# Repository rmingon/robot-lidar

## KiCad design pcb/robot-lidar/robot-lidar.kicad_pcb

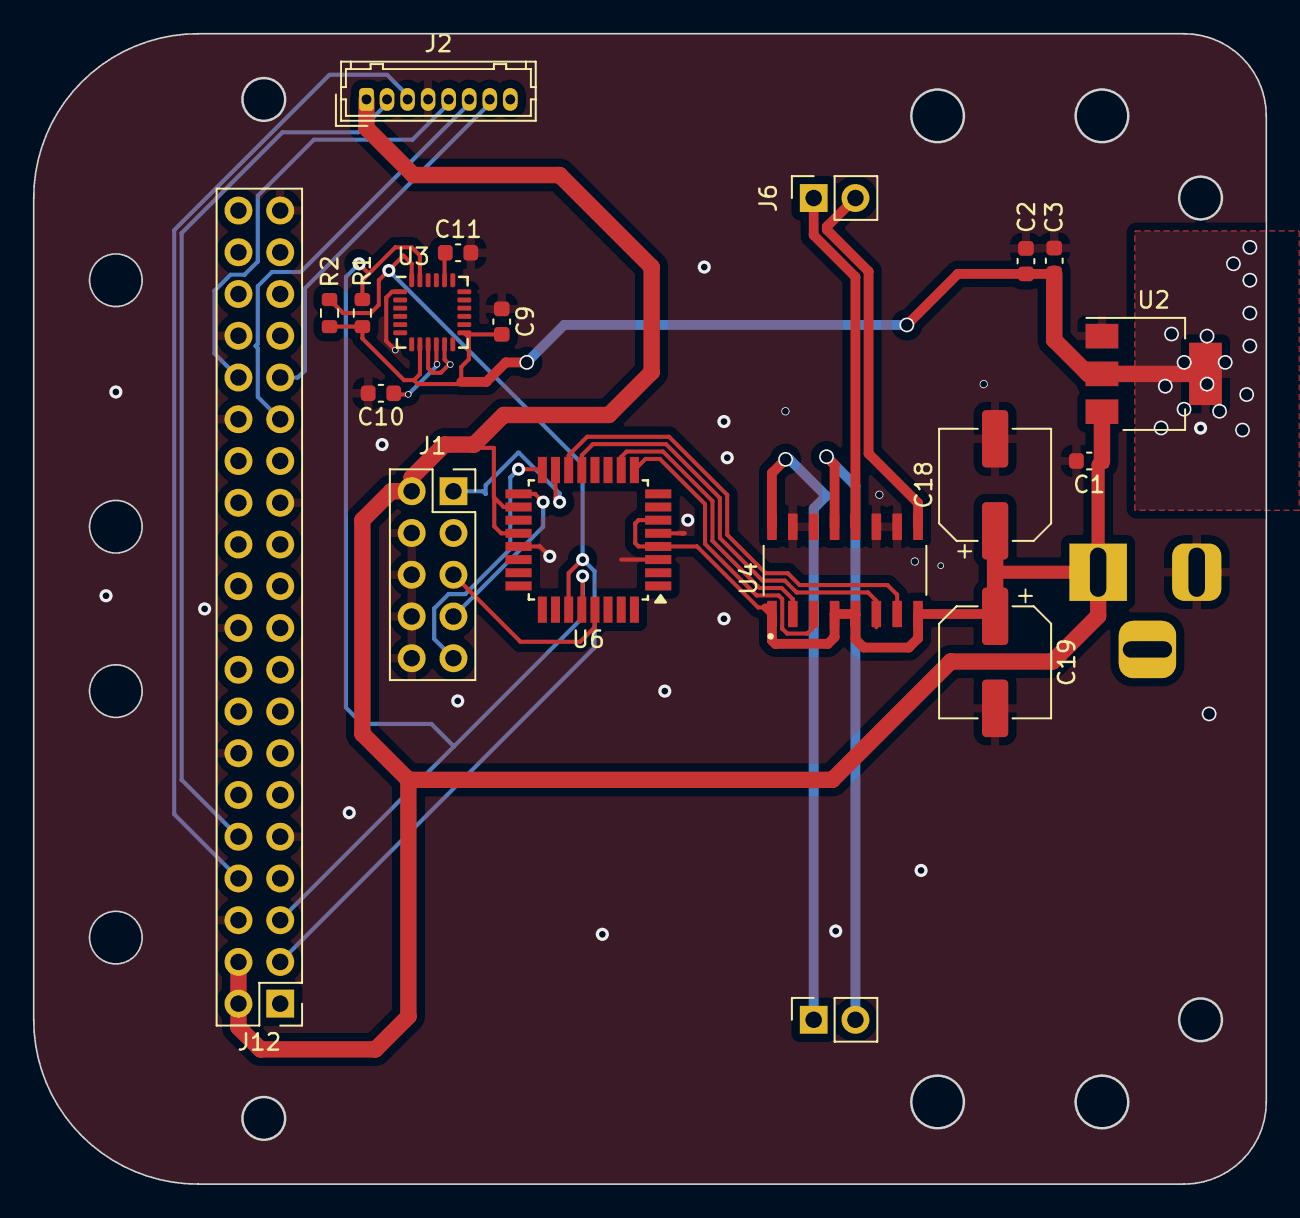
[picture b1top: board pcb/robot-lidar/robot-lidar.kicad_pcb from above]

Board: 2 copper layers, 75.0 x 70.0 mm, 20 parts (1 on the bottom side), 24 nets.

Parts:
C1: 1 uf; C_0603_1608Metric
C2: 1uf; C_0603_1608Metric
C3: 10 uf; C_0603_1608Metric
C9, C10, C11: C; C_0603_1608Metric
C18, C19: C_Polarized_Small; CP_Elec_6.3x4.9
J1: AVR-ISP-10; PinSocket_2x05_P2.54mm_Vertical
J2: YLIDAR X4; Hirose_DF13-08P-1.25DSA_1x08_P1.25mm_Vertical
J3: Jack-DC; BarrelJack_Horizontal
J5, J6: Conn_01x02; PinSocket_1x02_P2.54mm_Vertical
J12: Conn_02x20_Odd_Even; PinHeader_2x20_P2.54mm_Vertical
R1, R2: R_Small; R_0603_1608Metric
U2: LM317-3.3_SOT-223; SOT-223-3_TabPin2
U3: MPU-6050; InvenSense_QFN-24_4x4mm_P0.5mm
U4: MX1508; SOIC127P600X177-16N
U6: ATmega328P-A; TQFP-32_7x7mm_P0.8mm

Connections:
+3V3: C2.1, C3.1, C9.2, R1.1, R2.1, U2.2 (VO), U3.8 (VDDIO), U3.13 (VDD)
+5V: C1.1, C18.1, C19.1, J1.2 (VCC), J2.1, J3.1, J12.2, J12.4, U2.3 (VI), U4.1 (VCC1), U4.4 (VDD1), U4.5 (VCC2), U4.8 (VDD2), U6.4 (VCC), U6.6 (VCC), U6.18 (AVCC), U6.20 (AREF)
DEV_EN: J2.6, J12.29
GND: C1.2, C2.2, C3.2, C9.1, C10.2, C11.2, C18.2, C19.2, J1.4 (GND), J1.6 (GND), J1.8 (GND), J1.10 (GND), J2.4, J3.2, J12.6, J12.9, J12.14, J12.20, J12.25, J12.30, J12.34, J12.39, U2.1 (ADJ), U3.1 (CLKIN), U3.9 (AD0), U3.11 (FSYNC), U3.18 (GND), U4.10 (AGND2), U4.11 (PGND2), U4.14 (AGND1), U4.15 (PGND1), U6.3 (GND), U6.5 (GND), U6.21 (GND)
MISO: J1.9 (MISO), U6.16 (PB4)
MOSI: J1.1 (MOSI), U6.15 (PB3)
MOTOR_1_A: U4.2 (INA1), U6.10 (PD6)
MOTOR_1_B: U4.3 (INB1), U6.9 (PD5)
MOTOR_2_A: U4.6 (INA2), U6.13 (PB1)
MOTOR_2_B: U4.7 (INB2), U6.14 (PB2)
M_EN: J2.7, J12.31
M_SCTR: J2.5, J12.32
unnamed: J5.1, U4.16 (OUTA1)
unnamed: J5.2, U4.13 (OUTB1)
unnamed: J6.1, U4.12 (OUTA2)
unnamed: J6.2, U4.9 (OUTB2)
unnamed: C11.1, U3.20 (CPOUT)
unnamed: C10.1, U3.10 (REGOUT)
RST: J1.5 (~RST), U6.29 (~RESET/PC6)
SCK: J1.7 (SCK), U6.17 (PB5)
SCL: J12.5, R1.2, U3.23 (SCL), U6.28 (PC5)
SDA: J12.3, R2.2, U3.24 (SDA), U6.27 (PC4)
UART_RX: J2.2, J12.10
UART_TX: J2.3, J12.8

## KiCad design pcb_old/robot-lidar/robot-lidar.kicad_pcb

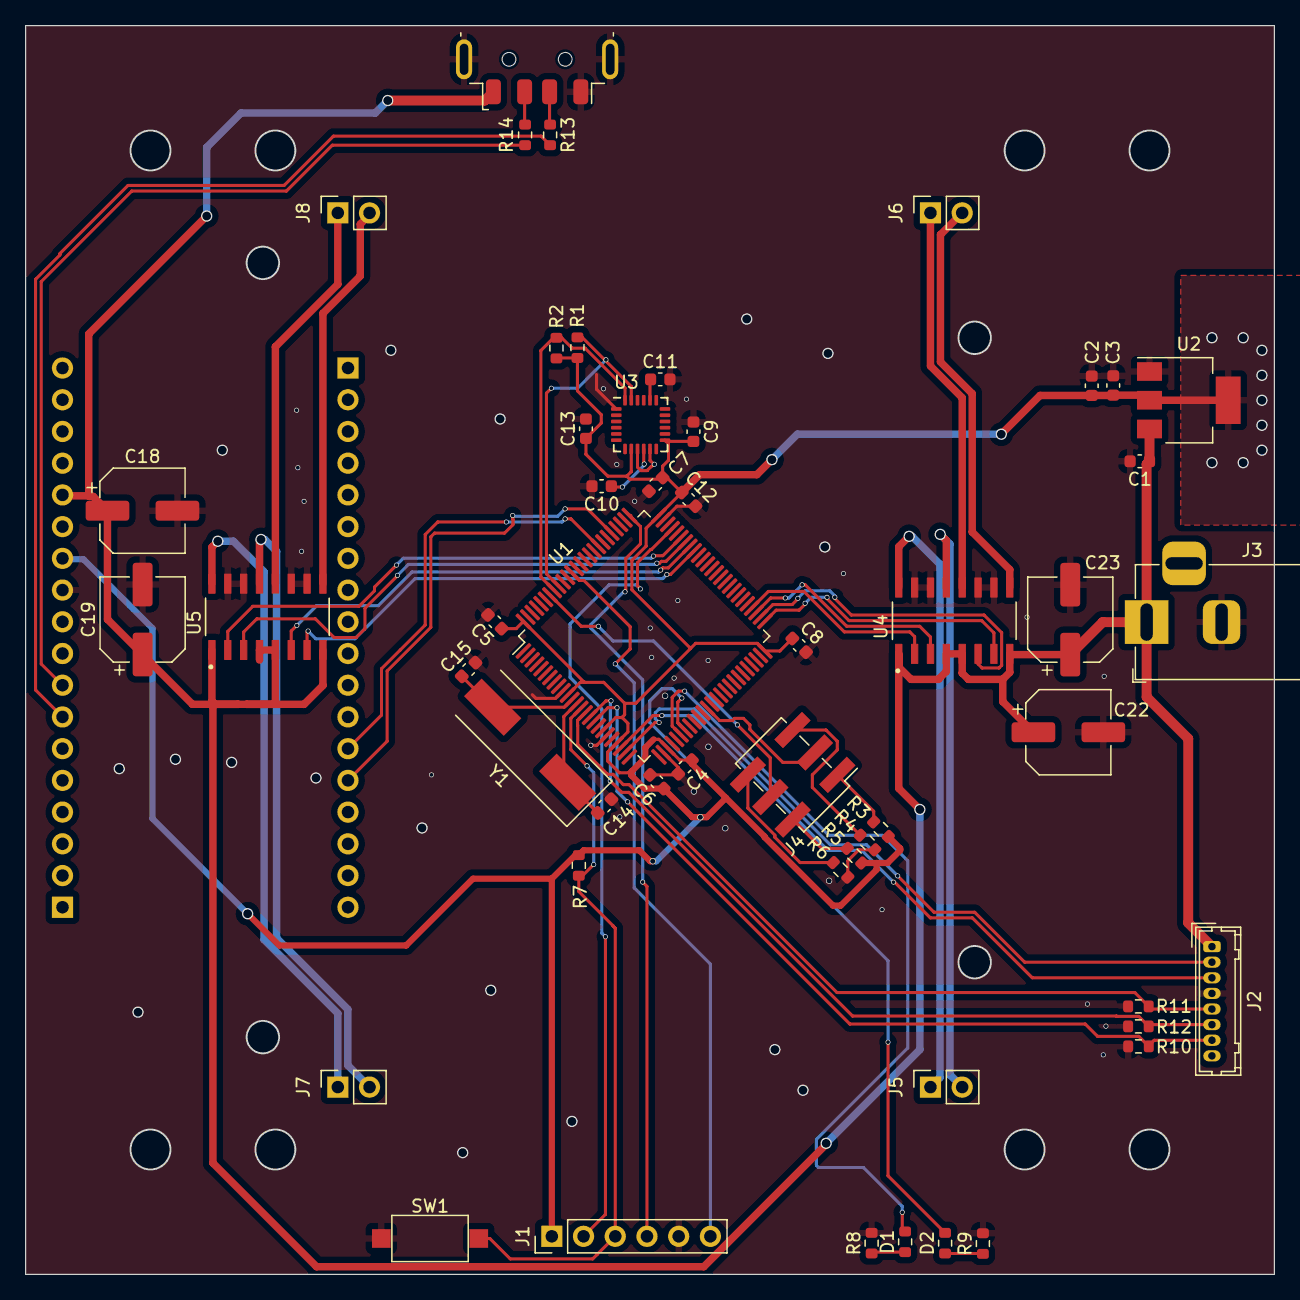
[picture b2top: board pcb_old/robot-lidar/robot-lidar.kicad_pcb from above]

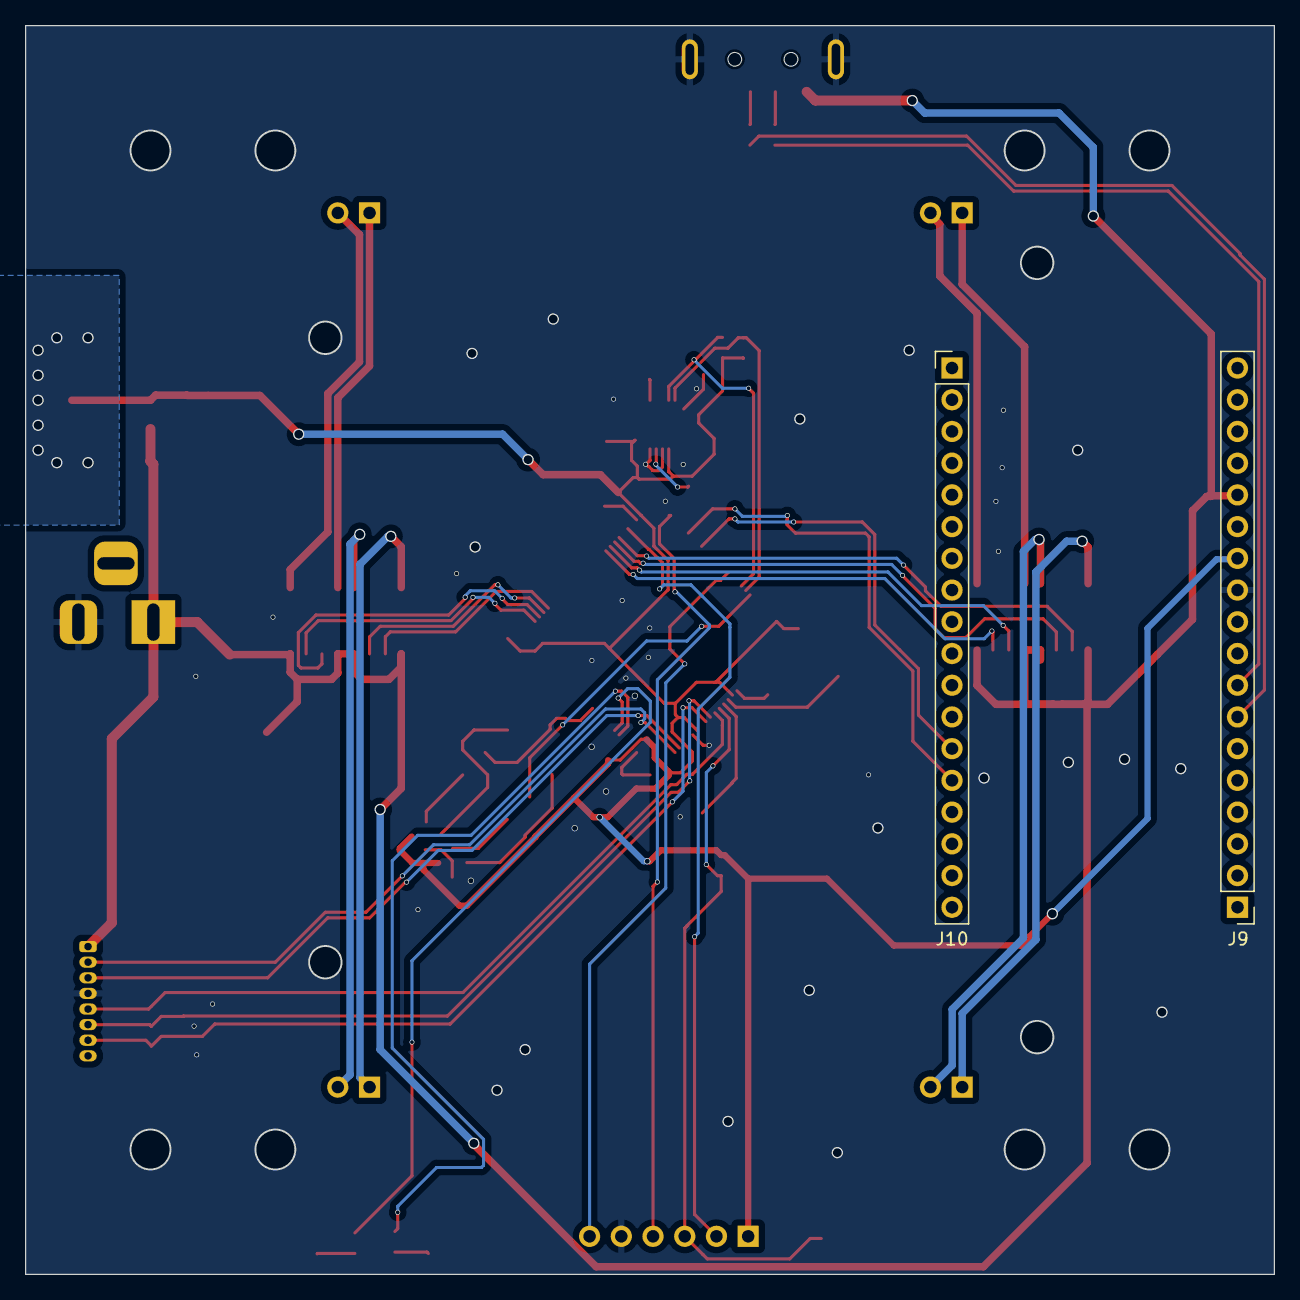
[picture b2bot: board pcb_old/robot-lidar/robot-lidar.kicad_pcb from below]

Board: 2 copper layers, 100.0 x 100.0 mm, 53 parts (2 on the bottom side), 50 nets.

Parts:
C1, C4, C5, C6, C7, C8, C12, C13: 1 uf; C_0603_1608Metric
C2: 1uf; C_0603_1608Metric
C3: 10 uf; C_0603_1608Metric
C9, C10, C11: C; C_0603_1608Metric
C14, C15: 0.1uF; C_0603_1608Metric
C18, C19, C22, C23: C_Polarized_Small; CP_Elec_6.3x4.9
D1, D2: LED_Small; R_0603_1608Metric
J1: Conn_ARM_SWD_TagConnect_TC2030; PinHeader_1x06_P2.54mm_Vertical
J2: YLIDAR X4; Hirose_DF13-08P-1.25DSA_1x08_P1.25mm_Vertical
J3: Jack-DC; BarrelJack_Horizontal
J4: Conn_02x03_Odd_Even; PinHeader_2x03_P2.54mm_Vertical_SMD
J5, J6, J7, J8: Conn_01x02; PinSocket_1x02_P2.54mm_Vertical
J9, J10: Conn_01x18; PinHeader_1x18_P2.54mm_Vertical
J11: USB_A; USB_A_Molex_48037-2200_Horizontal
R1, R2: R_Small; R_0603_1608Metric
R3, R4, R5, R6, R7: 10k; R_0603_1608Metric
R8, R9: 2k; R_0603_1608Metric
R10, R11, R12, R13, R14: 10K; R_0603_1608Metric
SW1: SW_SPST; SW_SPST_CK_RS282G05A3
U1: STM32F429VETx; LQFP-100_14x14mm_P0.5mm
U2: LM317-3.3_SOT-223; SOT-223-3_TabPin2
U3: MPU-6050; InvenSense_QFN-24_4x4mm_P0.5mm
U4, U5: MX1508; SOIC127P600X177-16N
Y1: Crystal; Crystal_SMD_HC49-SD

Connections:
+3V3: C2.1, C3.1, C4.1, C5.1, C6.1, C7.1, C8.1, C9.2, C12.1, C13.1, J1.1 (VCC), J9.12, R1.1, R2.1, R3.1, R5.2, R7.2, U1.11 (VDD), U1.19 (VDD), U1.22 (VDDA), U1.28 (VDD), U1.50 (VDD), U1.75 (VDD), U1.100 (VDD), U2.2 (VO), U3.8 (VDDIO), U3.13 (VDD)
+5V: C1.1, C18.1, C19.1, C22.1, C23.1, J2.1, J3.1, J9.14, J11.1 (VBUS), U2.3 (VI), U4.1 (VCC1), U4.4 (VDD1), U4.5 (VCC2), U4.8 (VDD2), U5.1 (VCC1), U5.4 (VDD1), U5.5 (VCC2), U5.8 (VDD2)
BOOT0: J4.4, U1.94 (BOOT0)
BOOT1: J4.3, U1.37 (PB2)
DEV_EN: J2.6, R12.1, U1.16 (PC1)
GND: C1.2, C2.2, C3.2, C4.2, C5.2, C6.2, C7.2, C8.2, C9.1, C10.2, C11.2, C12.2, C13.2, C14.2, C15.2, C18.2, C19.2, C22.2, C23.2, J1.5 (GND), J2.4, J3.2, J9.11, J11.4 (GND), J11.5 (Shield), R4.2, R6.1, R8.2, R9.2, R10.2, R11.2, R12.2, SW1.1 (A), U1.10 (VSS), U1.20 (VSSA), U1.27 (VSS), U1.74 (VSS), U1.99 (VSS), U2.1 (ADJ), U3.1 (CLKIN), U3.9 (AD0), U3.11 (FSYNC), U3.18 (GND), U4.10 (AGND2), U4.11 (PGND2), U4.14 (AGND1), U4.15 (PGND1), U5.10 (AGND2), U5.11 (PGND2), U5.14 (AGND1), U5.15 (PGND1)
I2C_SCL: R1.2, U1.92 (PB6), U3.23 (SCL)
I2C_SDA: R2.2, U1.93 (PB7), U3.24 (SDA)
MOTOR_1_A: U1.54 (PB15), U4.2 (INA1)
MOTOR_1_B: U1.53 (PB14), U4.3 (INB1)
MOTOR_2_A: U1.52 (PB13), U4.6 (INA2)
MOTOR_2_B: U1.51 (PB12), U4.7 (INB2)
MOTOR_3_A: U1.70 (PA11), U5.2 (INA1)
MOTOR_3_B: U1.69 (PA10), U5.3 (INB1)
MOTOR_4_A: U1.68 (PA9), U5.6 (INA2)
MOTOR_4_B: U1.67 (PA8), U5.7 (INB2)
M_EN: J2.7, R10.1, U1.17 (PC2)
M_SCTR: J2.5, R11.1, U1.15 (PC0)
unnamed: D1.2 (A), U1.31 (PA6)
unnamed: D1.1 (K), R8.1
unnamed: D2.2 (A), U1.32 (PA7)
unnamed: D2.1 (K), R9.1
unnamed: J4.1, R3.2
unnamed: J4.2, R5.1
unnamed: J4.5, R4.1
unnamed: J4.6, R6.2
unnamed: J5.1, U4.16 (OUTA1)
unnamed: J5.2, U4.13 (OUTB1)
unnamed: J6.1, U4.12 (OUTA2)
unnamed: J6.2, U4.9 (OUTB2)
unnamed: J7.1, U5.16 (OUTA1)
unnamed: J7.2, U5.13 (OUTB1)
unnamed: J8.1, U5.12 (OUTA2)
unnamed: J8.2, U5.9 (OUTB2)
unnamed: J11.3 (D+), R13.1
unnamed: J11.2 (D-), R14.1
unnamed: C11.1, U3.20 (CPOUT)
unnamed: C10.1, U3.10 (REGOUT)
PA13-SWDIO: J1.2 (SWDIO), U1.72 (PA13)
PA14-SWCLK: J1.4 (SWCLK), U1.76 (PA14)
PB3-SWO: J1.6 (SWO), U1.89 (PB3)
PH0: C15.1, U1.12 (PH0), Y1.2
PH1: C14.1, U1.13 (PH1), Y1.1
RESET: J1.3 (~RESET), R7.1, SW1.2 (B), U1.14 (NRST)
UART4_RX: J2.2, U1.24 (PA1)
UART4_TX: J2.3, U1.23 (PA0)
UART5_RX: J10.13, U1.83 (PD2)
UART5_TX: J10.14, U1.80 (PC12)
USB_DM: J9.8, R14.2
USB_DP: J9.7, R13.2

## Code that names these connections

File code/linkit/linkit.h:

void linkitInit() {
	UART5_Init();
}

void UART5_Init() {
    // Enable UART5 clock
    RCC->APB1ENR |= RCC_APB1ENR_UART5EN;

    // Enable GPIO clocks for UART5 (GPIOC)
    RCC->AHB1ENR |= RCC_AHB1ENR_GPIOCEN;

    // Configure PC12 as alternate function mode for UART5_TX
    GPIOC->MODER |= GPIO_MODER_MODER12_1; // Alternate function mode
    GPIOC->AFR[1] |= 0x8 << ((12 - 8) * 4); // AF8 for UART5_TX (PC12)

    // Configure PD2 as alternate function mode for UART5_RX
    GPIOD->MODER |= GPIO_MODER_MODER2_1; // Alternate function mode
    GPIOD->AFR[0] |= 0x8 << (2 * 4); // AF8 for UART5_RX (PD2)

    // Configure UART5 settings (baud rate, data bits, etc.)
    UART5->BRR = 1667; // For example, assuming 9600 baud rate (adjust as needed)
    UART5->CR1 |= USART_CR1_TE | USART_CR1_RE | USART_CR1_UE; // Enable UART5, transmitter, and receiver
}

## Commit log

2023-11-02 add mcu
2023-11-02 lidar pcb hole
2023-11-02 add jack
2023-11-02 add libar + regulator
2023-11-02 add gyro
2023-11-03 add i2c pin + crystal + SWD
2023-11-03 add rst
2023-11-03 add components
2023-11-03 wire crystal
2023-11-03 add leds
2023-11-03 add wiring motor
2023-11-03 add motor pin
2023-11-03 add pcb edge cut
2023-11-03 3.3 wiring
2023-11-03 wiring lidar
2023-11-03 wiring mcp6500
2023-11-08 add linkit
2023-11-08 add usb a connector
2023-11-08 add usb connector on pcb
2023-11-10 update wiring
2023-11-23 add real view
2023-11-24 add code
2024-03-18 add readme
2024-03-18 rename
2024-05-21 move to old
2024-05-21 update code + add linkit support
2024-05-21 add uart5 init
2024-05-26 stm32f4 to stm32f1 + linkit to raspberry
2024-05-26 saving shematic
2024-05-26 finish V2
2024-05-27 rewire i2c
2024-06-07 add ts
2024-06-13 PCA9685
2024-06-13 wiring pca
2024-07-10 remove typescript
2024-07-10 add i2c
2024-07-10 up state
2024-07-10 test pwm
2024-07-10 module mode
2024-07-10 update import
2024-07-10 await i2cInit
2024-07-10 write via buffer
2024-07-10 real buffer
2024-07-10 update pin
2024-07-10 test pin pwm
2024-07-10 fix promise
2024-07-10 add await
2025-03-01 remove two motor control and change i2c motor by atmgea328p
2025-03-02 wiring atmega and resize board
2025-03-16 add motor controller code
